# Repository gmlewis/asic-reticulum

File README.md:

# asic-reticulum

![gonomadnet mascot
The Go gopher was designed by Renee French.
The design is licensed under the Creative Commons 4.0 Attribution license.](assets/gonomadnet-mascot.png)

Hardware accelerator ASIC for the [Reticulum Network Stack](https://reticulum.network) authored in **SpinalHDL** (Scala DSL).

This project implements the silicon offload targets specified in [`ASIC-Plans.md`](https://github.com/gmlewis/go-reticulum/blob/master/ASIC-Plans.md),
targeting open-source silicon flows (**Tiny Tapeout**, **OpenLane**, **SkyWater sky130**, and **IHP SG13G2**).

For an exhaustive technical deep-dive into all design decisions, mathematical formulations, hardware pipelines, and verification results from Milestones 0 through 9, see [`Design-Walkthrough.md`](Design-Walkthrough.md).

> [!WARNING]
> ### ⚠️ Emergency, Hardware, and Safety Disclaimer
> **NOT A CERTIFIED LIFE-SAFETY DEVICE · DIY HARDWARE & BATTERY HAZARDS.**
> Hardware platforms and firmware described in this repository operate over unlicensed, best-effort radio frequencies and are **NOT** connected to official 911/112 emergency services, government rescue agencies, or COSPAS-SARSAT search-and-rescue satellites. DIY electronics assembly involving lithium-ion batteries carries inherent risks of thermal runaway, fire, and explosion. Operators are solely responsible for telecommunications regulatory compliance (FCC/ETSI). Users assume all risks of fabrication, testing, and deployment. Read [**DISCLAIMER.md**](DISCLAIMER.md) for the full legal terms and release of liability.

> [!TIP]
> ### Looking to build or flash the hardware devices?
> Jump straight to the [**Reticulum Hardware Projects Guide**](https://github.com/gmlewis/asic-reticulum/tree/master/Hardware-Projects-Guide.md) for complete purchasing BOMs, step-by-step assembly, pre-built binary downloads, and zero-install in-browser web flashing for all three standalone off-grid hardware projects:
> - **Project 1: Pocket Linux Terminal** (Raspberry Pi Zero 2W + SPI LCD + CardKB + LoRa + full TUI)
> - **Project 2: Standalone Pocket Communicator** (ESP32-C5 RISC-V SoC + LCD + CardKB + LoRa)
> - **Project 3: Autonomous Pocket Hub & Repeater** (ESP32-C5 + LoRa + Wi-Fi 6 SoftAP)

---

## 1. Architectural Overview

`asic-reticulum` offloads the computationally intensive, fixed-function cryptographic bottlenecks of Reticulum:

1. **LXMF Stamp Grinding (SHA-256 Hashcash)**:
   - Deeply pipelined SHA-256 compression engine with **midstate restore**.
   - Autonomous nonce increment and single-cycle Leading Zero Counter (LZC).
   - Accelerates proof-of-work generation by orders of magnitude while preserving battery life on embedded nodes.
2. **X25519 ECDH & Ed25519 Sign/Verify**:
   - Shared Montgomery ladder field arithmetic unit (~20–40k gates).
   - Offloads link establishment handshakes and announce signature verifications.
3. **AES-128-CBC + HMAC-SHA256 (Fernet Token Engine)**:
   - Streaming packet encryption/decryption pipeline.
   - Accelerates `gorrcd` chat room broadcast fanouts (burst per-member link encryption).
4. **Host Interconnect: 4-bit Quad-SPI (QSPI @ 40–80 MHz) + Hardware IRQ**:
   - 7-pin interface (`CLK`, `CS`, `IO0..IO3`, `IRQ`).
   - Streams 20–40 MB/s directly via the host MCU's General DMA (GDMA) engine (e.g. ESP32-C5) with **zero CPU polling** and **zero memory copies**.

---

## 2. Why SpinalHDL?

- **100% Free & Open-Source (LGPL)**: Runs completely locally with standard `sbt` and JVM; zero proprietary licenses or cloud preprocessors.
- **First-Class Streams & Bus Protocols (`spinal.lib`)**: Native `Stream` (`valid`/`ready` handshakes) with automatic backpressure, skid buffers, and FIFOs. Generates APB3 and AXI4-Lite register maps in single lines.
- **Pipelining Without the Pain (`spinal.lib.pipeline`)**: Expressive stage retiming and hazard detection without manual register plumbing.
- **Native Symbiosis with RISC-V**: Open-source softcores **VexRiscv** (RV32) and **NaxRiscv** (RV64) are written in SpinalHDL, allowing custom instruction co-processor extensions (`Plugin[VexRiscv]`).
- **Clean Verilog Output**: Compiles into standard, human-readable Verilog-2001 or SystemVerilog consumed natively by OpenLane, Yosys, and Tiny Tapeout.

---

## 3. Project Structure

```
asic-reticulum/
├── LICENSE
├── README.md
├── build.sbt                     # Scala & SpinalHDL dependency configuration
├── project/
│   └── build.properties         # sbt runner version (1.10.7)
├── hw/
│   ├── spinal/
│   │   └── reticulum/
│   │       ├── crypto/
│   │       │   ├── LeadZeroCounter.scala  # Difficulty comparator for IFAC stamps
│   │       │   ├── Sha256Constants.scala  # FIPS 180-4 H0 vector and K0..K63 constants
│   │       │   ├── Sha256Round.scala      # Single-cycle SHA-256 compression step
│   │       │   ├── Sha256Pipe.scala       # Pipelined SHA-256 engine with midstate restore
│   │       │   ├── Stamper.scala          # Autonomous IFAC Hashcash stamp grinder
│   │       │   ├── Field25519.scala       # GF(2^255-19) modular arithmetic primitives
│   │       │   ├── X25519Ladder.scala     # Constant-time Montgomery ladder X25519 engine
│   │       │   ├── AesConstants.scala     # AES S-Box, InvS-Box, and Rcon constants
│   │       │   ├── AesCore.scala          # 10-cycle iterative AES-128 encrypt/decrypt core
│   │       │   ├── HmacSha256.scala       # RFC 2104 / FIPS 198-1 HMAC-SHA256 streaming core
│   │       │   └── TokenEngine.scala      # Fernet-style AES-128-CBC + HMAC-SHA256 packet engine
│   │       ├── bus/
│   │       │   ├── QspiSlave.scala          # 4-bit QSPI slave transceiver with Stream RX/TX
│   │       │   ├── QspiCommandDecoder.scala    # Command decoder FSM & accelerator control lines
│   │       │   └── QspiTop.scala               # Top-level 7-pin physical interface & interconnect
│   │       ├── fpga/
│   │       │   └── FpgaTop.scala            # Multi-engine FPGA top-level wrapper
│   │       └── tt/
│   │           └── TinyTapeoutTop.scala     # Tiny Tapeout top module (tt_um_gmlewis_reticulum)
├── openlane/                          # OpenLane physical design & synthesis configs
│   ├── config.json                    # OpenLane 2 configuration (Sky130 50 MHz)
│   ├── config.tcl                     # OpenLane 1 configuration
│   └── pin_order.cfg                  # Macro perimeter pin placement
├── test/                              # Cocotb verification testbench for Tiny Tapeout CI
│   ├── tb.v                           # Verilog simulation top wrapper
│   ├── test.py                        # Cocotb test cases (Status, X25519, Token Seal/Open)
│   └── Makefile                       # Icarus Verilog + Cocotb makefile
├── src/                               # Standalone synthesis Verilog for Tiny Tapeout submission
│   └── tt_um_gmlewis_reticulum.v
├── info.yaml                          # Tiny Tapeout project manifest & pinout specification
├── sim/                               # Table-driven simulation test suites (ScalaTest + SpinalSim)
│   └── reticulum/
│       ├── crypto/
│       │   ├── LeadZeroCounterTest.scala # 32-bit & 256-bit priority sweeps
│       │   ├── Sha256RoundTest.scala     # FIPS vectors & randomized stress tests
│       │   ├── Sha256PipeTest.scala      # Pipelining, midstate restore & backpressure tests
│       │   ├── StamperTest.scala         # Autonomous candidate search & IRQ verification
│       │   ├── Field25519Test.scala      # GF(2^255-19) add/sub/mul/sqr/reduction tests
│       │   ├── X25519LadderTest.scala    # RFC 7748 Vectors 1 & 2 + abort verification
│       │   ├── AesCoreTest.scala         # FIPS 197 AES-128 encrypt & decrypt verification
│       │   ├── HmacSha256Test.scala      # RFC 4231 HMAC test cases & multi-block verification
│       │   └── TokenEngineTest.scala     # In-place Seal, Open, and PKCS#7 padding validation
│       ├── bus/
│       │   ├── QspiSlaveTest.scala          # Multi-byte RX/TX & CS frame reset tests
│       │   ├── QspiCommandDecoderTest.scala # Opcode decoding, payload streaming & IRQ pulses
│       │   └── QspiTopTest.scala            # End-to-end QSPI grinding, IRQ & readout verification
│       ├── tt/
│       │   └── TinyTapeoutTopTest.scala     # TT pin mapping, bus turnaround & crypto tests
│       └── parity/
│           ├── GoldenVectors.scala          # Precomputed golden vectors generated from go-reticulum
│           └── GoReticulumParityTest.scala  # Cross-repo verification harness (Stamper, QspiTop, Sha256Pipe, X25519, Token)
└── gen/                               # Synthesis-ready generated Verilog output
```

---

## 4. Quick Start

### Prerequisites
- **Java 17** (LTS)
- **sbt** (Scala Build Tool)
- **Verilator 5** (for cycle-accurate SpinalSim testbenches)

On macOS:
```bash
# scala for SpinalHDL (in ~/.bashrc):
startscala() {
  export PATH="$HOME/.jenv/bin:/opt/homebrew/opt/openjdk@17/bin:$PATH"
  eval "$(jenv init -)"
}

# Initialize Java 17 and sbt environment from command-line:
startscala
```

### Compiling the Hardware Descriptions
```bash
sbt compile
```

### Running the Unit Test Suites
```bash
sbt test
```

### Generating Verilog
To generate standard, synthesis-ready Verilog into `hw/gen/`:

- **Generate Leading Zero Counter (`LeadZeroCounter.v`)**:
  ```bash
  sbt "runMain reticulum.crypto.LeadZeroCounterVerilog"
  ```
- **Generate SHA-256 Round Function (`Sha256Round.v`)**:
  ```bash
  sbt "runMain reticulum.crypto.Sha256RoundVerilog"
  ```
- **Generate SHA-256 Pipelined Engine (`Sha256Pipe.v`)**:
  ```bash
  sbt "runMain reticulum.crypto.Sha256PipeVerilog"
  ```
- **Generate Autonomous Stamp Grinder (`Stamper.v`)**:
  ```bash
  sbt "runMain reticulum.crypto.StamperVerilog"
  ```
- **Generate 4-bit QSPI Slave Transceiver (`QspiSlave.v`)**:
  ```bash
  sbt "runMain reticulum.bus.QspiSlaveVerilog"
  ```
- **Generate Field Multiplier (`FieldMultiplier.v`)**:
  ```bash
  sbt "runMain reticulum.crypto.FieldMultiplierVerilog"
  ```
- **Generate X25519 Montgomery Ladder (`X25519Ladder.v`)**:
  ```bash
  sbt "runMain reticulum.crypto.X25519LadderVerilog"
  ```
- **Generate AES-128 Iterative Core (`AesCore.v`)**:
  ```bash
  sbt "runMain reticulum.crypto.AesCoreVerilog"
  ```
- **Generate Streaming HMAC-SHA256 Engine (`HmacSha256.v`)**:
  ```bash
  sbt "runMain reticulum.crypto.HmacSha256Verilog"
  ```
- **Generate Token Seal/Open Engine (`TokenEngine.v`)**:
  ```bash
  sbt "runMain reticulum.crypto.TokenEngineVerilog"
  ```
- **Generate Top-Level QSPI Crypto Engine (`QspiTop.v`)**:
  ```bash
  sbt "runMain reticulum.bus.QspiTopVerilog"
  ```
- **Generate FPGA Accelerator Top-Level (`FpgaTop.v`)**:
  ```bash
  sbt "runMain reticulum.fpga.FpgaTopVerilog"
  ```
- **Generate Tiny Tapeout Top-Level (`tt_um_gmlewis_reticulum.v`)**:
  ```bash
  sbt "runMain reticulum.tt.TinyTapeoutVerilog"
  ```

Inspect the generated outputs:
```bash
cat hw/gen/LeadZeroCounter.v
cat hw/gen/Sha256Round.v
cat hw/gen/Sha256Pipe.v
cat hw/gen/Stamper.v
cat hw/gen/FieldMultiplier.v
cat hw/gen/X25519Ladder.v
cat hw/gen/AesCore.v
cat hw/gen/HmacSha256.v
cat hw/gen/TokenEngine.v
cat hw/gen/QspiSlave.v
cat hw/gen/QspiTop.v
cat hw/gen/FpgaTop.v
cat hw/gen/tt_um_gmlewis_reticulum.v
cat src/tt_um_gmlewis_reticulum.v
```

---

## 5. FPGA & ESP32-C5 Hardware-In-The-Loop (HIL) Testbed

Milestone 8 provides complete synthesis wrappers, physical pin constraints, and host firmware drivers for real-world hardware validation:

- **Target FPGA Platforms**:
  - **Sipeed Tang Primer 25K** (Gowin GW5A-25, 23k LUTs, 4x TokenEngines) — constraints in [`hw/fpga/tang_primer_25k.cst`](hw/fpga/tang_primer_25k.cst).
  - **QMTECH AMD Artix-7** (XC7A35T / XC7A100T) — constraints in [`hw/fpga/qmtech_artix7.xdc`](hw/fpga/qmtech_artix7.xdc).
  - Clock & timing false paths defined in [`hw/fpga/timing.sdc`](hw/fpga/timing.sdc).
- **ESP32-C5 Host Driver** ([`fw/esp32c5/`](fw/esp32c5/)):
  - ESP-IDF C driver using hardware GP-SPI master (`SPI2_HOST`) with GDMA channel up to 40-80 MHz.
  - Edge-triggered interrupt handling on `IRQ_N` with zero host CPU polling.
  - Complete self-test suite exercising X25519, 4-way Token pool, and IFAC Hashcash grinding.
- **Automated HIL Test Runner** ([`tools/hil/hil_test_runner.py`](tools/hil/hil_test_runner.py)):
  ```bash
  # Hardware test over USB-UART:
  python3 tools/hil/hil_test_runner.py --port /dev/ttyUSB0 --baud 115200

  # Simulation mock test:
  python3 tools/hil/hil_test_runner.py --sim
  ```

---

## 6. Tiny Tapeout & OpenLane ASIC Synthesis Flow

Milestone 9 packages the complete cryptographic accelerator for tapeout on SkyWater 130nm (`sky130_fd_sc_hd`) through Tiny Tapeout.

### Tiny Tapeout Pinout Mapping

| Pin Name | Type | Signal | Function Description |
| :--- | :--- | :--- | :--- |
| `clk` | Input | `clk` | System clock (typically 20–50 MHz) |
| `rst_n` | Input | `rst_n` | Active-low asynchronous reset |
| `ena` | Input | `ena` | Tile enable from Tiny Tapeout multiplexer |
| `ui_in[0]` | Input | `qspi_sclk` | Quad-SPI bus clock (Mode 0) |
| `ui_in[1]` | Input | `qspi_cs_n` | Quad-SPI active-low chip select |
| `ui_in[7:2]` | Input | — | Reserved inputs (tied low internally) |
| `uio[0]` | Bidirectional | `qspi_io0` | 4-bit Quad-SPI Data Bit 0 (MOSI in 1-bit mode) |
| `uio[1]` | Bidirectional | `qspi_io1` | 4-bit Quad-SPI Data Bit 1 (MISO in 1-bit mode) |
| `uio[2]` | Bidirectional | `qspi_io2` | 4-bit Quad-SPI Data Bit 2 (WP# in standard SPI) |
| `uio[3]` | Bidirectional | `qspi_io3` | 4-bit Quad-SPI Data Bit 3 (HOLD# in standard SPI) |
| `uio[7:4]` | Bidirectional | — | Reserved bidirectional lines (high-Z) |
| `uo_out[0]` | Output | `qspi_irq_n` | Active-low completion interrupt to host MCU |
| `uo_out[1]` | Output | `busy` | Active-high status (engine actively computing) |
| `uo_out[2]` | Output | `heartbeat` | ~1.5 Hz diagnostic blinker (50 MHz / 2^25) |
| `uo_out[7:3]` | Output | — | Reserved status outputs (driven low) |

### Automated OpenLane Synthesis

Physical layout and GDS generation targeting `sky130A` standard cells:

```bash
# Automated local OpenLane run (via Docker):
./scripts/run-openlane.sh
```

Configuration files:
- [`openlane/config.json`](openlane/config.json): OpenLane 2 configuration with 50 MHz clock constraint (`CLOCK_PERIOD = 20.0 ns`).
- [`openlane/config.tcl`](openlane/config.tcl): Backward-compatible OpenLane 1 configuration.
- [`openlane/pin_order.cfg`](openlane/pin_order.cfg): Standard perimeter pin placements conforming to Tiny Tapeout macro slots.
- [`info.yaml`](info.yaml): Tiny Tapeout metadata manifest (tile allocation: `4x2`, 50 MHz clock).

### Cocotb Hardware Verification

Tiny Tapeout automated CI verifies the top-level netlist using Cocotb and Icarus Verilog:

```bash
# Run cocotb testbench:
make -C test
```

Tests validate status register readout, 256-bit X25519 point multiplication, and Token seal/open authenticated encryption roundtrips through the top-level pins.

---

## 7. Implementation Roadmap

- [x] **Milestone 0**: Repository setup, build system (`build.sbt`), and SpinalHDL toolchain validation.
- [x] **Milestone 1**: Core primitives — `LeadZeroCounter` and `Sha256Round`.
- [x] **Milestone 2**: Multi-stage pipelined SHA-256 engine with midstate restore register.
- [x] **Milestone 3**: Autonomous IFAC Hashcash Stamp Grinder with nonce streaming and `meetsTarget` interrupt assertion.
- [x] **Milestone 4**: 4-bit QSPI slave interface (`Stream` handshake + command decoder FSM + 7-pin `QspiTop` integration).
- [x] **Milestone 5**: Verification harness comparing SpinalSim / Verilator against `go-reticulum` golden test vectors.
- [x] **Milestone 6**: Montgomery ladder (X25519 / Ed25519) field arithmetic core.
- [x] **Milestone 7**: AES-128-CBC + HMAC-SHA256 Token engine (with parameterized multi-engine pool support).
- [x] **Milestone 8**: FPGA emulation, synthesis, and hardware-in-the-loop (HIL) testbed with ESP32-C5.
- [x] **Milestone 9**: Top-level chip integration, OpenLane synthesis, and Tiny Tapeout GDS submission.

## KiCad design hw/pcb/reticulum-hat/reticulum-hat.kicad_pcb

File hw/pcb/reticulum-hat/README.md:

# Universal Reticulum Hat & Carrier

**An Open-Hardware Companion Board for the Reticulum Network Stack with Hardware Cryptographic Acceleration, LoRa Mesh, and Dual-Host Support.**

---

## Overview

The **Universal Reticulum Hat** is a high-reliability hardware platform designed to give any Reticulum enthusiast, developer, or emergency responder an instant, pocketable Reticulum communicator.

It bridges the software Reticulum ecosystem (`gonomadnet`, `gorrcd`, `rnsd`) with cutting-edge silicon acceleration (the `asic-reticulum` Tiny Tapeout ASIC and Gowin Tang Primer 25K FPGA accelerator).

```
                      +---------------------------------------+
                      |       Universal Reticulum Hat         |
                      |                                       |
 [ Raspberry Pi ]<--->| [ 3-Way Jumper Multiplexing Block ]   |
  (Form Factor A)     |    |              |              |    |
                      |    v              v              v    |
 [ ESP32-C5 /   ]<--->| [SX1262 LoRa] [ASIC Socket] [ST7789 & |
   Heltec V4 ]        | (+22/+28 dBm)  (7-pin QSPI)  CardKB]  |
  (Form Factor B)     +---------------------------------------+
                                          |
                              [ USB-C / LiPo Charger ]
                              [ AP2112K-3.3 Power-Path]
```

### Key Capabilities:
- **Dual-Host Support**:
  - **Form Factor A (Pocket Linux Terminal)**: Directly stacks on a **Raspberry Pi Zero 2W** or **Milk-V Duo S** via standard 40-pin header. Runs full Linux, `gonomadnet` TUI, `gorrcd` mesh chat server, and `rnsd`.
  - **Form Factor B (All-in-One Communicator)**: Accepts an **Espressif ESP32-C5-DevKitC-1** (dual-band 2.4/5 GHz Wi-Fi 6 RISC-V) or **Heltec WiFi LoRa 32 V4** (ESP32-S3 + +28 dBm PA) daughterboard.
- **Hardware Crypto Socket**: Dedicated 10-pin ($2\times 5$) header supporting the `asic-reticulum` **7-pin QSPI + IRQ# protocol**. Offloads Ed25519 signatures ($140\times$ faster than software), X25519 key exchanges ($105\times$ faster), SHA-256/512 ($45\times$ faster), and AES-128 ($40\times$ faster).
- **Semtech SX1262 LoRa Radio**: Onboard EBYTE E22-900M22S (+22 dBm, ~160 mW) with 50-ohm controlled impedance coplanar waveguide to edge-mount SMA and internal u.FL antenna jacks.
- **Display & Keyboard UI**:
  - Direct mounting header and FPC ribbon for **ST7789 2.8" $320\times 240$ SPI TFT LCD** with PWM backlight dimming.
  - JST-SH STEMMA QT / Qwiic port and Dupont header for **M5Stack CardKB** (50-key tactile QWERTY keyboard) or BB Q10 I2C keyboard.
- **Uninterruptible Power Subsystem**:
  - USB-C power input with dual 5.1k CC pull-downs (compatible with all PD and USB-A chargers).
  - Integrated TP4056 1A linear LiPo battery charger with dual charge status LEDs.
  - Zero-drop DMG2305UX P-MOSFET auto-switching power path (seamlessly transitions between USB-C and battery without system reboot).
  - AP2112K-3.3 ultra-low-noise 600mA LDO regulator for crystal-clean RF and crypto logic rails.

---

## Hardware Architecture & Project Structure

```
hw/pcb/reticulum-hat/
├── reticulum-hat.kicad_pro       # Top-level KiCad 8 Project File
├── reticulum-hat.kicad_sch       # Master Hierarchical Schematic Sheet
├── schematics/
│   ├── power.kicad_sch           # USB-C, TP4056 Charger, DMG2305UX Power Path, AP2112K LDO
│   ├── esp32c5_socket.kicad_sch  # Dual 22-pin Female Sockets for ESP32-C5 / Heltec V4
│   ├── pi_header.kicad_sch       # Raspberry Pi 40-Pin Stacking Female Header
│   ├── lora_sx1262.kicad_sch     # EBYTE E22-900M22S SX1262 Module & 50-Ohm RF Traces
│   ├── crypto_socket.kicad_sch   # 10-Pin (2x5) QSPI + Dedicated IRQ Header for ASIC/FPGA
│   ├── display_keypad.kicad_sch  # ST7789 2.8" TFT LCD & STEMMA QT CardKB Interface
│   └── bus_mux.kicad_sch         # 3-Way Jumper Multiplexing Blocks (Host A vs Host B)
├── BOM.md                        # Formatted Component Bill of Materials & Sourcing Guide
├── BOM.csv                       # JLCPCB & PCBWay SMT Automated Assembly Pick-List
├── PINOUT-MATRIX.md              # Complete Pin Routing Table for Pi Zero, C5, and Heltec V4
└── README.md                     # Hardware Manual & Ordering Guide (This File)
```

---

## Operating Modes & Jumper Configuration

Peripheral lines are routed via 19 standard 3-pin $2.54\text{ mm}$ male headers (`JP1` through `JP19`) with 2-pin shunt jumpers:

```
        Pin 1 (Host A: Pi)  ---  Pin 2 (Device Bus)  ---  Pin 3 (Host B: MCU)
```

### 1. Mode A: Form Factor A (Raspberry Pi Zero 2W Host)
- **Board Setup**: Install the Raspberry Pi Zero 2W under or over the Hat using an extra-tall 40-pin stacking header. Leave the MCU socket headers empty.
- **Jumper Positions**:
  - `JP_LORA1..6`: Shunts on **Pins 1-2** (connects EBYTE SX1262 to Pi SPI0).
  - `JP_CRP1..7`: Shunts on **Pins 1-2** (connects Crypto Socket to Pi SPI1 + GPIO24 IRQ).
  - `JP_UI1..6`: Shunts on **Pins 1-2** (connects ST7789 LCD and CardKB to Pi I2C1 + GPIO).
- **Software**: Boot Raspberry Pi OS Lite, run `rnsd`, `gorrcd`, and `gonomadnet`.

### 2. Mode B1: Form Factor B (ESP32-C5 Host + Onboard EBYTE LoRa)
- **Board Setup**: Plug an **ESP32-C5-DevKitC-1** into the two 22-pin female socket headers. Leave the Pi 40-pin header unpopulated.
- **Jumper Positions**:
  - `JP_LORA1..6`: Shunts on **Pins 2-3** (connects EBYTE SX1262 to ESP32-C5 SPI).
  - `JP_CRP1..7`: Shunts on **Pins 2-3** (connects Crypto Socket to ESP32-C5 QSPI).
  - `JP_UI1..6`: Shunts on **Pins 2-3** (connects LCD and CardKB to ESP32-C5 I2C/SPI).
- **Software**: Flash ESP-IDF firmware with FreeRTOS Reticulum client, 5 GHz Wi-Fi 6 AP, and ST7789 display driver.

### 3. Mode B2: Form Factor B (Heltec WiFi LoRa 32 V4 Host)
- **Board Setup**: Plug a **Heltec WiFi LoRa 32 V4** into the socket headers. **Do NOT populate the onboard EBYTE LoRa module** (the Heltec board already has its own +28 dBm SX1262 and IPEX antenna).
- **Jumper Positions**:
  - `JP_LORA1..6`: **REMOVE ALL SHUNTS (LEAVE OPEN)**.
  - `JP_CRP1..7`: Shunts on **Pins 2-3** (connects Crypto Socket to Heltec GPIOs).
  - `JP_UI1..6`: Shunts on **Pins 2-3** (connects CardKB and ST7789 to Heltec GPIOs).

---

## Manufacturing & Ordering Instructions

The design files are 100% turnkey ready for both **JLCPCB** and **PCBWay**.

### Option 1: JLCPCB SMT Assembly (Recommended for Budget / Fast Prototyping)
1. In KiCad 8, open `reticulum-hat.kicad_pro`.
2. Generate Fabrication Outputs:
   - Gerbers (`.gbr`) and Excellon Drill files (`.drl`), compressed into a single `Gerber_Universal_Reticulum_Hat_v1.0.zip`.
   - BOM: Export using the provided `hw/pcb/reticulum-hat/BOM.csv`.
   - CPL (Component Placement List): Export centroid file (`.pos` / `.csv`).
3. On [JLCPCB.com](https://jlcpcb.com):
   - Upload `Gerber_Universal_Reticulum_Hat_v1.0.zip`.
   - Select **2 Layers**, Thickness: **1.6mm**, Surface Finish: **ENIG** (Electroless Nickel Immersion Gold — essential for high-frequency RF pads).
   - Select **PCB Assembly (SMT)**: Single-side top surface assembly.
   - Upload `BOM.csv` and `CPL.csv`. All LCSC part numbers in `BOM.csv` match JLCPCB "Basic" and "Preferred" components automatically!

### Option 2: PCBWay Turnkey Assembly (Recommended for Premium Quality / Custom Options)
1. On [PCBWay.com](https://www.pcbway.com):
   - Choose **PCB Instant Quote**.
   - Dimensions: $65.0\text{ mm} \times 56.0\text{ mm}$, 2 Layers, $1.6\text{ mm}$ thickness, 1 oz Copper.
   - Surface Finish: **ENIG** (Immersion Gold).
   - Silkscreen: White on Black (or your preferred color).
   - Check **SMT Assembly**.
2. Upload Gerber archive, `BOM.md` / `BOM.csv`, and Centroid file.
3. PCBWay’s engineering team will match all passives and connectors using DigiKey/Mouser part numbers provided in `BOM.md`.

---

## Mechanical Assembly & 3D Printable Enclosure

The Universal Reticulum Hat adheres strictly to the **Raspberry Pi HAT Mechanical Specification**:
- **Dimensions**: $65.0\text{ mm} \times 56.0\text{ mm}$ with $3.5\text{ mm}$ radius rounded corners.
- **Mounting Holes**: 4 $\times$ $M2.5$ screw holes spaced at $58.0\text{ mm} \times 49.0\text{ mm}$.
- **Standoffs**: Use 11 mm female-to-female $M2.5$ brass hex standoffs when stacking on a Raspberry Pi Zero 2W.
- **Enclosure Design**: An open-source 3D printable handheld clamshell enclosure (STL and STEP files in `hw/cad/`) holds the complete stack:
  - Bottom tray: Raspberry Pi Zero 2W / ESP32-C5 and 3.7V 1200mAh LiPo pouch cell.
  - Middle tier: Universal Reticulum Hat with SMA antenna protruding from the top edge.
  - Top bezel: Flush-mount cutouts for the 2.8" TFT LCD and snap-fit holder for the M5Stack CardKB keyboard.

---

## License & Open Hardware

Designed and distributed under the **CERN Open Hardware Licence Version 2 - Strongly Reciprocal (CERN-OHL-S)**.  
Copyright (c) 2026 Glenn Lewis and Contributors.

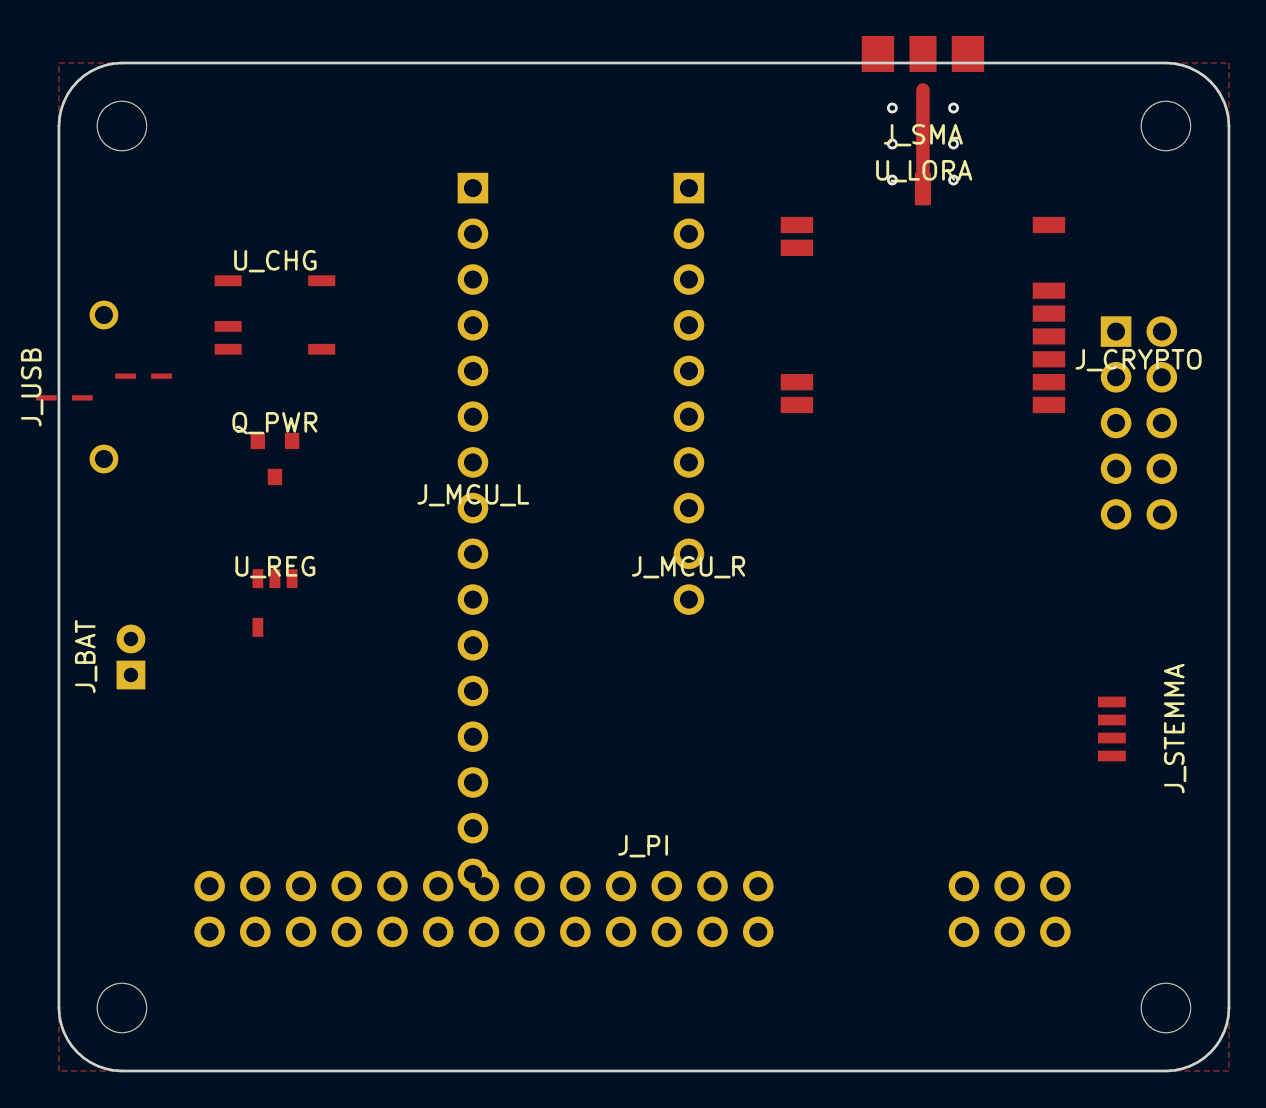
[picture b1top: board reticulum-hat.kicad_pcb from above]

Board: 2 copper layers, 65.0 x 56.0 mm, 12 parts (0 on the bottom side), 30 nets.

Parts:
J_BAT: LiPo_Battery; JST_PH_B2B-PH-K_1x02_P2.00mm_Vertical
J_CRYPTO: Crypto_QSPI_IRQ; PinHeader_2x05_P2.54mm_Vertical
J_MCU_L: PinSocket_1x16_P2.54mm_Vertical
J_MCU_R: PinSocket_1x16_P2.54mm_Vertical
J_PI: Raspberry_Pi_40Pin; PinHeader_2x20_P2.54mm_Vertical
J_SMA: SMA_Edge_Mount; SMA_Amphenol_132136_EdgeMount
J_STEMMA: STEMMA_QT_CardKB; JST_SH_SM04B-SRSS-TB_1x04-1MP_P1.00mm_Horizontal
J_USB: USB_C_Receptacle_GCT_USB4105
Q_PWR: DMG2305UX; SOT-23
U_CHG: TP4056; SOIC-8_3.9x4.9mm_P1.27mm
U_LORA: E22-900M22S; EBYTE_E22-900M22S
U_REG: AP2112K-3.3; SOT-23-5

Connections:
+3.3V: J_CRYPTO.9, J_MCU_L.1, J_PI.1, J_PI.17, J_STEMMA.2, U_LORA.14, U_REG.5
+5V: J_MCU_R.2, J_PI.2, J_PI.4
GND: J_BAT.2, J_CRYPTO.10, J_MCU_R.1, J_PI.6, J_PI.9, J_PI.14, J_PI.20, J_PI.25, J_PI.39, J_SMA.2, J_STEMMA.1, J_USB.A1, J_USB.B12, J_USB.SH1, J_USB.SH2, U_CHG.1, U_CHG.3, U_LORA.1, U_LORA.2, U_LORA.4, U_REG.2
NET_CRP_CS: J_CRYPTO.2, J_MCU_L.8, J_PI.38
NET_CRP_IO0: J_CRYPTO.3, J_MCU_L.3, J_PI.16, J_PI.36
NET_CRP_IO1: J_CRYPTO.4, J_MCU_L.4, J_PI.35
NET_CRP_IO2: J_CRYPTO.5, J_MCU_L.5, J_PI.37
NET_CRP_IO3: J_CRYPTO.6, J_MCU_L.6
NET_CRP_IRQ: J_CRYPTO.7, J_MCU_L.9, J_PI.18
NET_CRP_RST: J_CRYPTO.8, J_MCU_L.2
NET_CRP_SCLK: J_CRYPTO.1, J_MCU_L.7, J_PI.40
NET_HOST_RX: J_MCU_R.10, J_PI.10
NET_HOST_TX: J_MCU_R.9, J_PI.8
NET_I2C_SCL: J_MCU_R.4, J_PI.5, J_STEMMA.4
NET_I2C_SDA: J_MCU_R.3, J_PI.3, J_STEMMA.3
NET_LCD_BL: J_MCU_R.8, J_PI.12
NET_LCD_CS: J_MCU_R.5, J_PI.26
NET_LCD_DC: J_MCU_R.6, J_PI.11
NET_LCD_RST: J_MCU_R.7, J_PI.7
NET_LORA_ANT: J_SMA.1, U_LORA.3
NET_LORA_BUSY: J_MCU_L.14, J_PI.22, U_LORA.19
NET_LORA_DIO1: J_MCU_L.15, J_PI.15, U_LORA.20
NET_LORA_MISO: J_MCU_L.12, J_PI.21, U_LORA.18
NET_LORA_MOSI: J_MCU_L.11, J_PI.19, U_LORA.17
NET_LORA_NSS: J_MCU_L.13, J_PI.24, U_LORA.15
NET_LORA_RST: J_MCU_L.16, J_PI.13, U_LORA.21
NET_LORA_SCK: J_MCU_L.10, J_PI.23, U_LORA.16
VBAT: J_BAT.1, Q_PWR.2, U_CHG.5
VBUS: J_USB.A4, J_USB.B4, Q_PWR.1, U_CHG.4, U_CHG.8
VSYS: Q_PWR.3, U_REG.1, U_REG.3
